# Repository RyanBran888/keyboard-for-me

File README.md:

# keyboard-for-me

Im ryan i wanted to make a keybaord so i made a keyboard

it has buttons so i can type on the keyboard and they are shapped weirdly because i wanted too make them like that

this is the cad

here is the schematic and pcb design

# BOM
43 cherry mx switches, $0.40 each, https://mechanicalkeyboards.com/products/cherry-mx2a-blue-60g-clicky?variant=48020492058924
pcb, $22 before shipping, https://cart.jlcpcb.com/quote?orderType=1&homeUploadNum=16e498e1b85e4a028cc747985ca3c315&businessType=example&fileName=keyboard%20meow.zip
43 diodes, $5.99, https://www.amazon.com/BOJACK-Switching-IN4148-Electronic-Silicon/dp/B07Q4F3Y5W/ref=sr_1_1_sspa?dib=eyJ2IjoiMSJ9.8C1ebcszlPAbe4ldgX4jaM9nlgUAEZPfJqUMbjw_ZdpkWEwcssYvTxbYnJF53VrlREb14I7mVynYJgJ5Kp11OSsATFMvqVnDN6B5O5zB-FIXj6ijuhH8Dyq4ca3NyhJdHzz_aF1C9L6bNXHJhDWVBNnWthZb21NCIkbkpTNpyhyhy13EQccQccFY4fqMg_Yvza8Co1w-dGJhilLgP1ygudSUzukedrXrcY6g2_a9jEE.rtiyEm4IqLsRecI3w_YXtwChUCNeShi37NFI-OPCsAU&dib_tag=se&keywords=1n4148+diodes&qid=1750034530&sr=8-1-spons&sp_csd=d2lkZ2V0TmFtZT1zcF9hdGY&psc=1

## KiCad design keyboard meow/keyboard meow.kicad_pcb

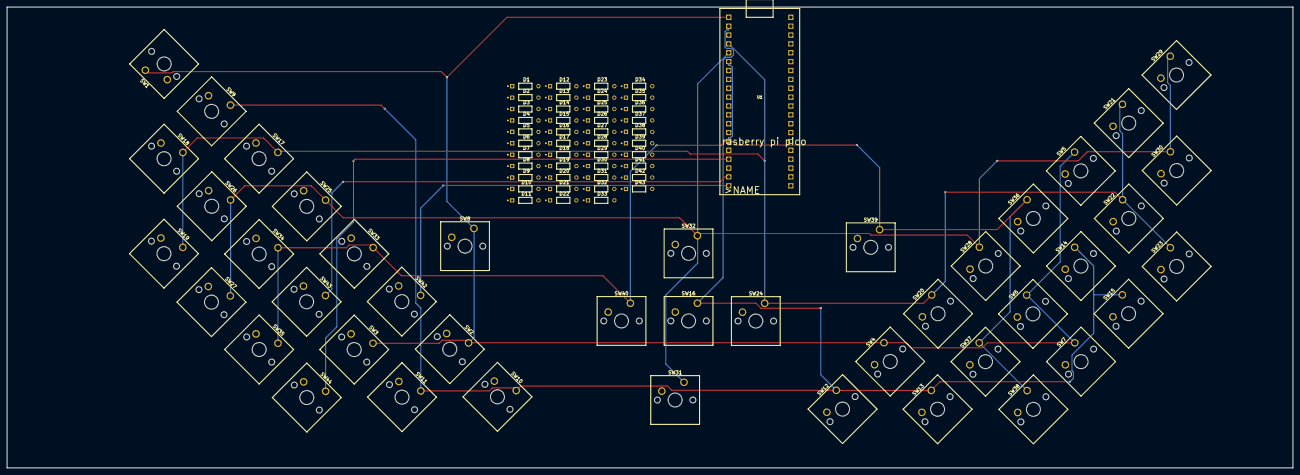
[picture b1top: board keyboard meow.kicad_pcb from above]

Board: 2 copper layers, 368.3 x 132.0 mm, 87 parts (0 on the bottom side), 8 nets.

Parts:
D1, D2, D3, D4, D5, D6, D7, D8, D9, D10, D11, D12, D13, D14, D15, D16, D17, D18, D19, D20, D21, D22, D23, D24, D25, D26, D27, D28, D29, D30, D31, D32, D33, D34, D35, D36, D37, D38, D39, D40, D41, D42, D43: D; DIOAD753W49L380D172B
SW1, SW2, SW3, SW4, SW5, SW6, SW7, SW8, SW9, SW10, SW11, SW12, SW13, SW14, SW15, SW16, SW17, SW18, SW19, SW20, SW21, SW22, SW23, SW24, SW25, SW26, SW27, SW28, SW29, SW30, SW31, SW32, SW33, SW34, SW35, SW36, SW37, SW38, SW39, SW40, SW42, SW43, SW44: SW_Push_45deg; SW_Cherry_MX_1.00u_PCB
U1: RASPBERRY_PI_PICO

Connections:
1: SW44.1, U1.GP13
2: SW43.1, U1.GP14
3: SW42.1, U1.GP15
col1: SW1.1, SW2.1, SW3.1, SW4.1, SW5.1, SW6.1, SW7.1, SW8.1, U1.GP0
col2: SW9.1, SW10.1, SW11.1, SW12.1, SW13.1, SW14.1, SW15.1, SW16.1, U1.GP1
col3: SW17.1, SW18.1, SW19.1, SW20.1, SW21.1, SW22.1, SW23.1, SW24.1, U1.GP2
col4: SW25.1, SW26.1, SW27.1, SW28.1, SW29.1, SW30.1, SW31.1, SW32.1, U1.GP3
col5: SW33.1, SW34.1, SW35.1, SW36.1, SW37.1, SW38.1, SW39.1, SW40.1, U1.GP4, U1.GP11
